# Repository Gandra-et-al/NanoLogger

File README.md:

NanoLogger
==========

A low-cost versatile data logging system for ecological applications

==========

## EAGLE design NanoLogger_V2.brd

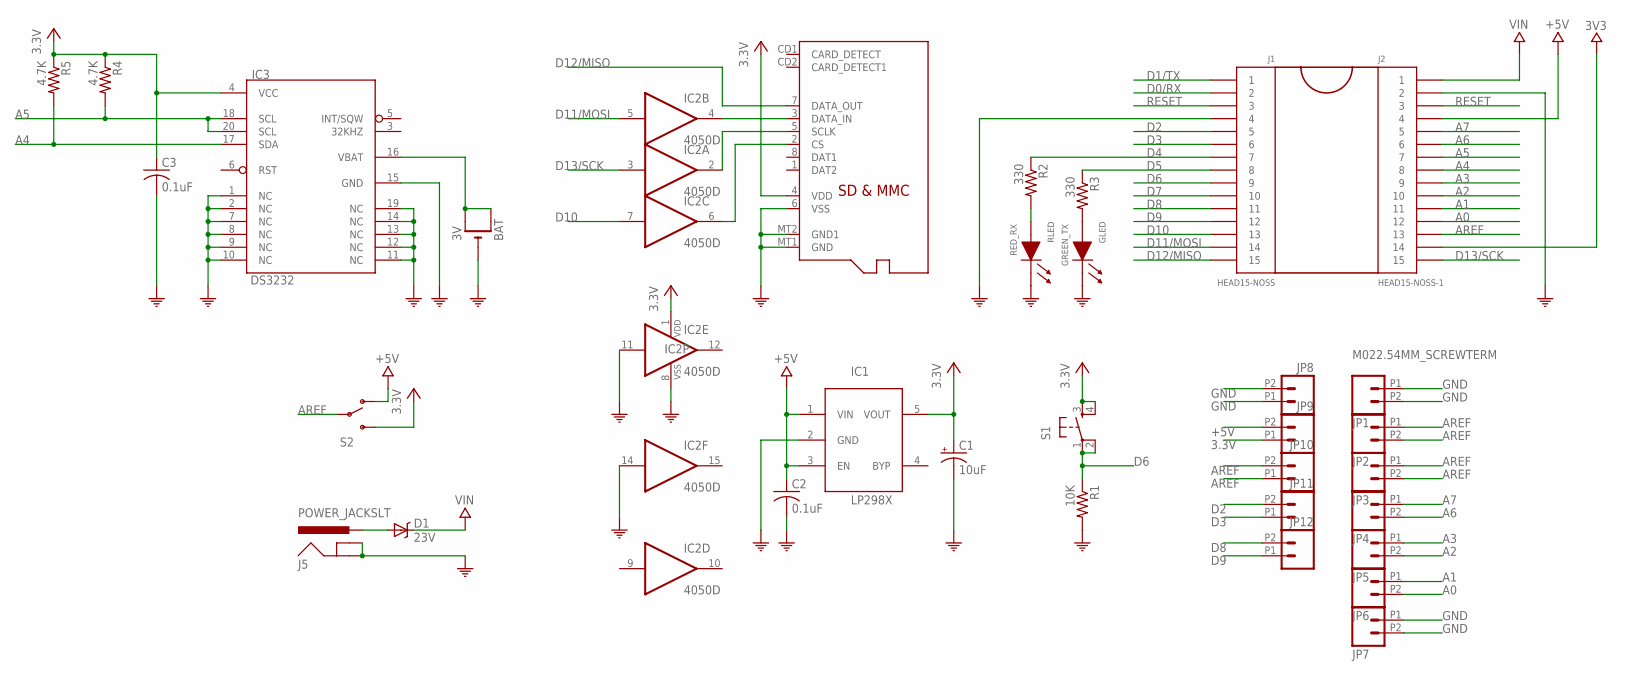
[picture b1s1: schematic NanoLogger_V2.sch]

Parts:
BAT: 3V; CR1220-SMD
C1: 10uF; A/3216-18R
C2, C3: 0.1uF; C0805K
D1: 23V; SOD-323
GLED: GREEN_TX; LED0805
IC1: LP298XS; SOT23-5L
IC2: 4050D; SO16
IC3: DS3232; SO20L
J1: HEAD15-NOSS
J2: HEAD15-NOSS-1
J5: POWER_JACKSLT; POWER_JACK_SLOT
JP1, JP2, JP3, JP4, JP5, JP6, JP7, JP8, JP9, JP10, JP11, JP12: M022.54MM_SCREWTERM; 1X02_2.54_SCREWTERM
R1: 10K; R0805
R2, R3: 330; R0805
R4, R5: 4.7K; R0805
RLED: RED_RX; LED0805
S1: TAC_SWITCHSMD; TACTILE_SWITCH_SMD
S2: SWITCH-SPDTPTH; SWITCH-SPDT
X1: MICROSD

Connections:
3.3V: C1.+, C3.1, IC1.5 (VOUT), IC2.1 (VDD), IC3.4 (VCC), JP9.P1 (1), R4.1, R5.1, S1.3, S1.4, S2.3 (S), X1.4 (VDD)
3V3: J2.14
+5V: C2.1, IC1.1 (VIN), IC1.3 (EN), J2.4, JP9.P2 (2), S2.1 (O)
A0: J2.12, JP6.P2 (2)
A1: J2.11, JP6.P1 (1)
A2: J2.10, JP5.P2 (2)
A3: J2.9, JP5.P1 (1)
A4: IC3.17 (SDA), J2.8, R5.2
A5: IC3.18 (SCL), IC3.20 (SCL), J2.7, R4.2
A6: J2.6, JP4.P2 (2)
A7: J2.5, JP4.P1 (1)
AREF: J2.13, JP2.P1 (1), JP2.P2 (2), JP3.P1 (1), JP3.P2 (2), JP10.P1 (1), JP10.P2 (2), S2.2
BAT_POWER: D1.2 (A), J5.PWR
D0/RX: J1.2
D1/TX: J1.1
D2: J1.5, JP11.P2 (2)
D3: J1.6, JP11.P1 (1)
D4: J1.7, R2.1
D5: J1.8, R3.1
D6: J1.9, R1.1, S1.1, S1.2
D7: J1.10
D8: J1.11, JP12.P2 (2)
D9: J1.12, JP12.P1 (1)
D10: IC2.7 (I), J1.13
D11/MOSI: IC2.5 (I), J1.14
D12/MISO: J1.15, X1.7 (DATA_OUT)
D13/SCK: IC2.3 (I), J2.15
GND: BAT.-, C1.-, C2.2, C3.2, GLED.1 (CA), IC1.2 (GND), IC2.8 (VSS), IC2.11 (I), IC2.14 (I), IC3.1 (NC), IC3.2 (NC), IC3.7 (NC), IC3.8 (NC), IC3.9 (NC), IC3.10 (NC), IC3.11 (NC), IC3.12 (NC), IC3.13 (NC), IC3.14 (NC), IC3.15 (GND), IC3.19 (NC), J1.4, J2.2, J5.GND@1 (GNDBREAK), J5.GND@2 (GND), JP1.P1 (1), JP1.P2 (2), JP7.P1 (1), JP7.P2 (2), JP8.P1 (1), JP8.P2 (2), R1.2, RLED.1 (CA), X1.6 (VSS), X1.MT1 (GND), X1.MT2 (GND1)
unnamed: IC2.2 (O), X1.5 (SCLK)
unnamed: IC2.6 (O), X1.2 (CS)
unnamed: IC2.4 (O), X1.3 (DATA_IN)
unnamed: GLED.2 (AN), R3.2
unnamed: R2.2, RLED.2 (AN)
RESET: J1.3, J2.3
VBAT: BAT.+$1 (+), BAT.+$2 (+1), IC3.16 (VBAT)
VIN: D1.1 (C), J2.1

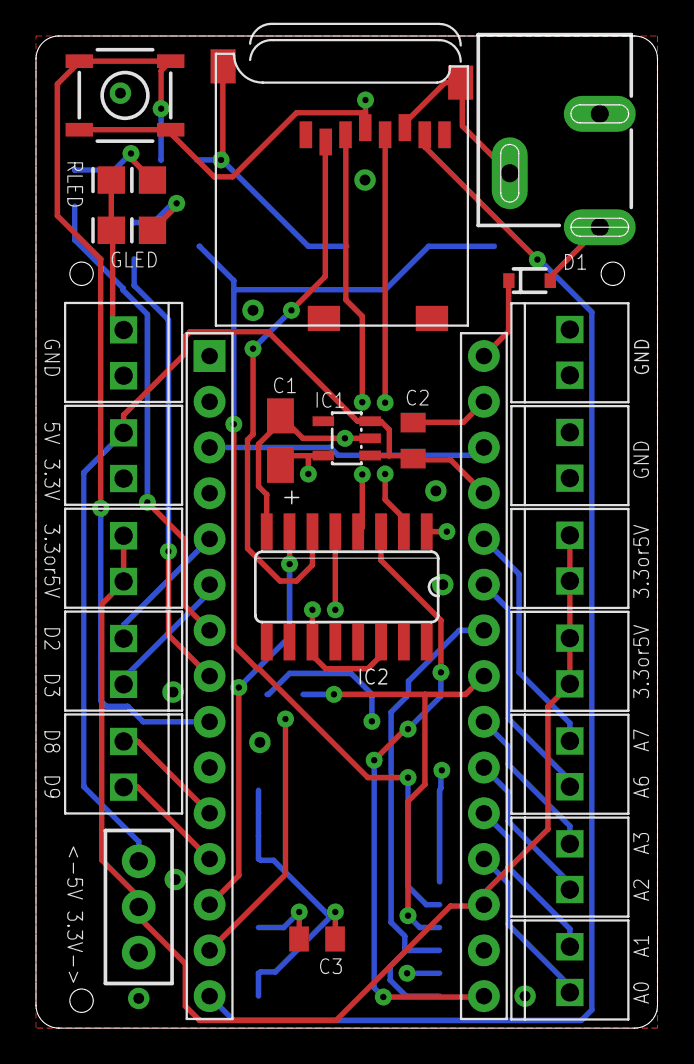
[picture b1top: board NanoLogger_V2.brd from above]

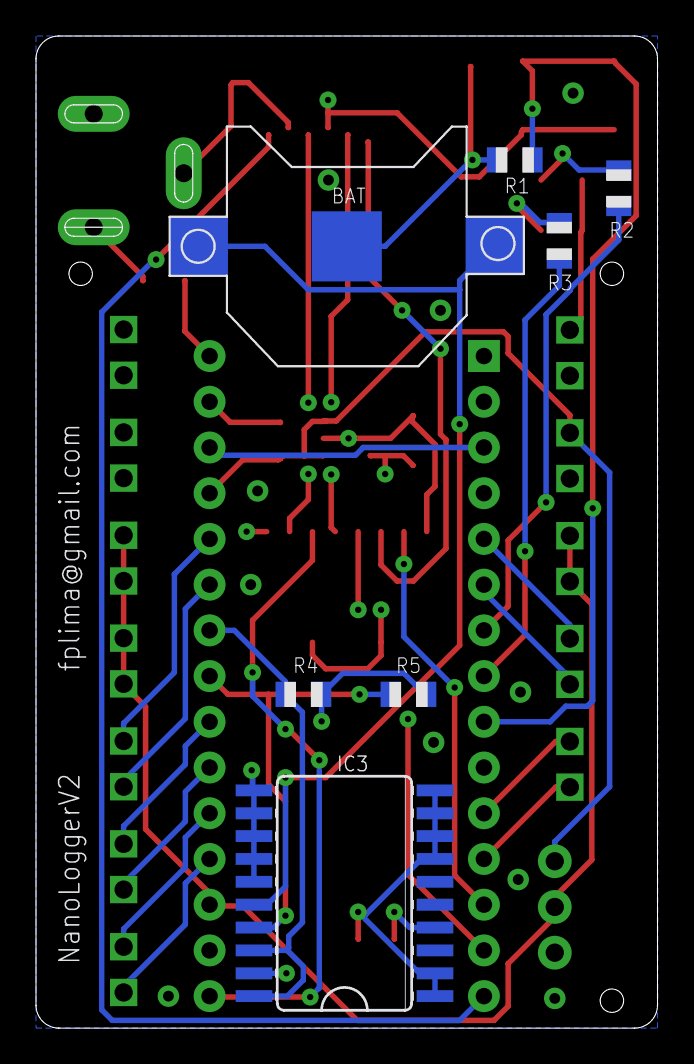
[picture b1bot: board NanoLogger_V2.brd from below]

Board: 4 copper layers, 34.5 x 55.1 mm, 33 parts (7 on the bottom side), 32 nets.

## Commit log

2014-05-20 Eagle Files
2014-05-20 Hardware Folder
2014-05-20 Software v1
2014-05-21 Required Arduino Libraries
2014-05-21 Added Board Schematic
2014-05-22 More commented version
2014-05-22 Last script version
2014-05-22 Added Settings File
2014-05-22 Board Schematic
2014-05-22 Settings File
2014-05-22 Thermoucouple Example Script
2014-05-22 Rm Settings
2014-05-28 Thermocouple Script Version
2014-06-09 Main software version
2014-06-09 Software modified to work with the Adafruit MAX31855 Thermocouple Amplifier board
2014-06-09 Settings file example
2014-06-09 NanoLogger photo
2014-06-09 Modified Arduino IDE file to set clock speed

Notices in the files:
parts and their libraries:
SparkFun-Connectors: Licensing: CC v3.0 Share-Alike You are welcome to use this library for commercial purposes.
